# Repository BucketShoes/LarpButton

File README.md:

# LARP timer
Electronics project for live action roleplay, objective capture botton/timer.
Think like a chess clock, but more lights, bigger display, sound/voice callouts. Press and hold to capture an objective point, with time tracking.
ESP32 C6 based project, bluetooth admin interface for time tracking, number of swaps, team colors, and bluetooth beacons/player tracking.
PCB through JCLPCB, mostly from the basic parts list.
Built for battlecrylarp.org

# WORK IN PROGRESS
Note yet complete, untested.

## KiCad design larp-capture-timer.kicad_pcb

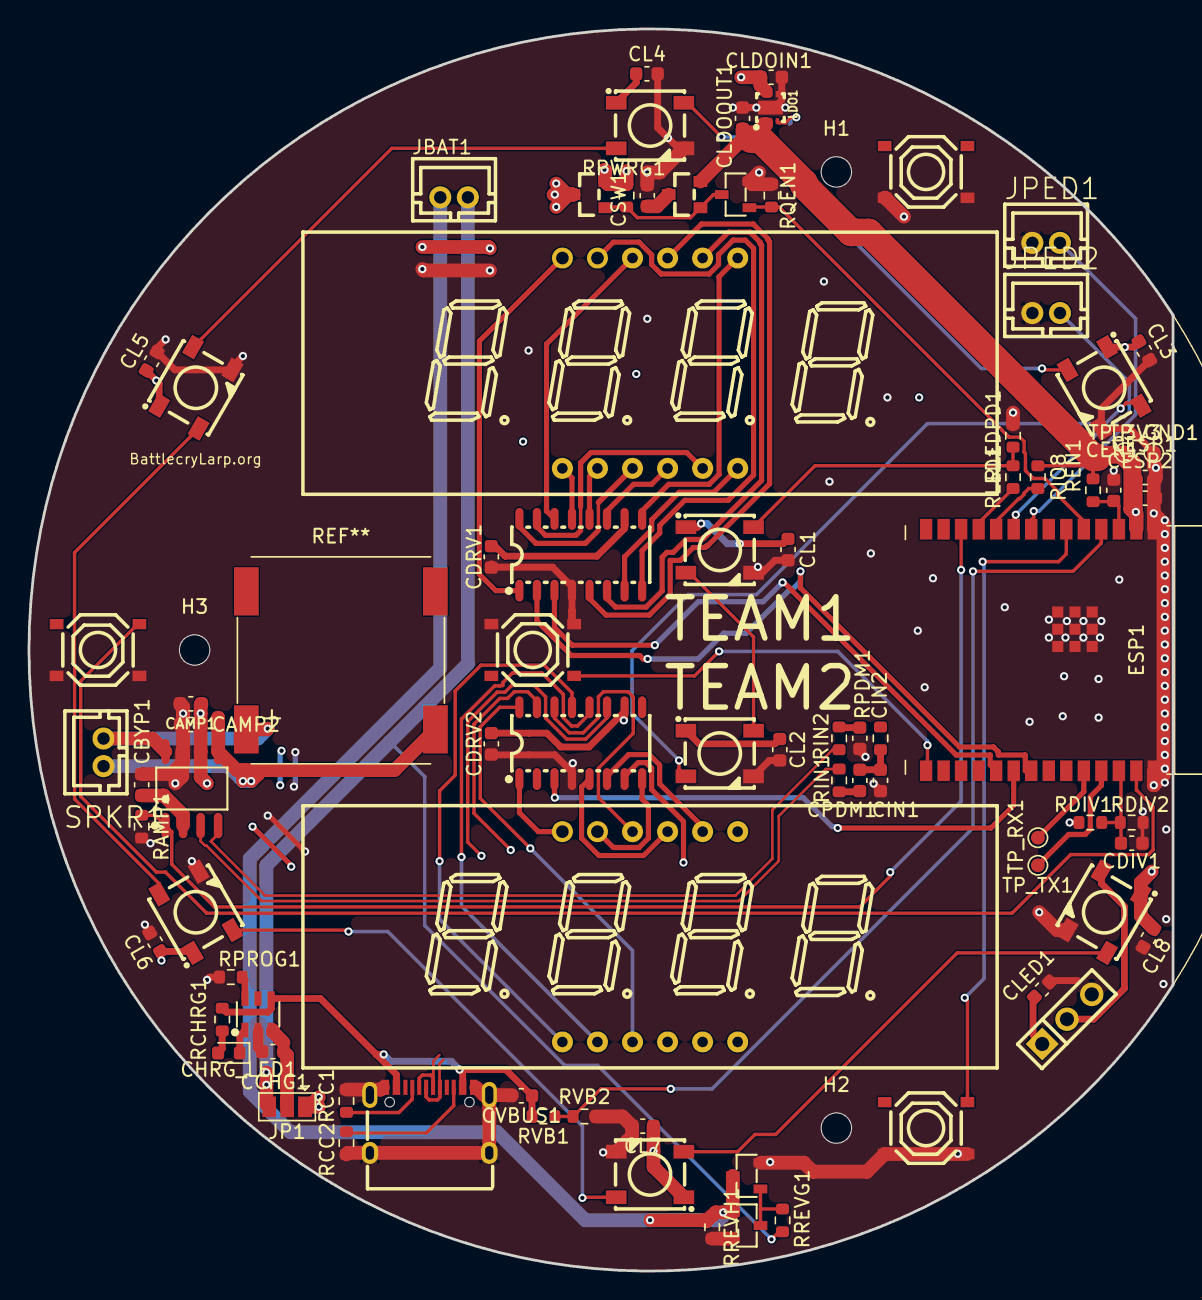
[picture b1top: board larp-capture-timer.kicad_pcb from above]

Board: 4 copper layers, 82.9 x 90.0 mm, 87 parts (1 on the bottom side), 78 nets.

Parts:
AMP1: NS4150C; SOP-8_L4.9-W3.9-P1.27-LS6.0-BL_NS4150C
BOOT1: TS-1187A-B-A-B; SW-SMD_4P-L5.1-W5.1-P3.70-LS6.5-TL_H1.5
BTN1, BTN2, BTN3: TS-1187A-B-A-B; SW-SMD_4P-L5.1-W5.1-P3.70-LS6.5-TL_H1.5
CAMP1: 10uF; C_0603_1608Metric
CAMP2: 1uF; C_0603_1608Metric
CBYP1: 1uF; C_0603_1608Metric
CCHG1: 10uF; C_0603_1608Metric
CDIV1: 100nF; C_0603_1608Metric
CDRV1, CDRV2: 100nF; C_0603_1608Metric
CELL1: BH-18650-B6AA002; BATTERY-SMD_18650-1S-L77.1-W20.7-1
CEN1: 1uF; C_0603_1608Metric
CESP1: 10uF; C_0603_1608Metric
CESP2: 100nF; C_0603_1608Metric
CHRG1: TP4057-42-SOT26-R; SOT-23-6_L2.9-W1.6-P0.95-LS2.8-BL_TP4057-42-SOT26-R
CHRG_LED1: Red; LED_0603_KA
CIN1, CIN2: 100nF; C_0603_1608Metric
CL1, CL2, CL3, CL4, CL5, CL6, CL7, CL8: 100nF; C_0603_1608Metric
CLDOIN1: 10uF; C_0603_1608Metric
CLDOOUT1: 10uF; C_0603_1608Metric
CLED1: 10uF; C_0603_1608Metric
CPDM1: 10nF; C_0603_1608Metric
CSW1: 10uF; C_0603_1608Metric
CVBUS1: 10uF; C_0603_1608Metric
DISP1, DISP2: FJ5462AH; LED-SEG-TH_12P-L50.3-W19.0-P2.54-S15.24-BL_FJ5462AH
DRV1, DRV2: GN1650; SOP-16_L9.9-W3.9-P1.27-LS6.1-BL_GN1650
ESP1: ESP32-C6-WROOM-1-N8; ESP32-C6-WROOM-1
H1, H2, H3: M2; MountingHole_2.2mm_M2
JBAT1: B2B-PH-K-S; CONN-TH_B2B-PH-K-S
JLEDX1: LED ext 1x3; HDR-TH_3P-P2.54-V-M_PZ254V-11-03P
JP1: SolderJumper_3; SolderJumper-3_P1.3mm_Open_Pad1.0x1.5mm
JPED1, JPED2: B2B-PH-K-S; CONN-TH_B2B-PH-K-S
LDO1: XC6220B331ER-G; USP-6C_L2.0-W1.8-P0.50-BL-EP_XC6220B331ER-G
LED1, LED2, LED3, LED4, LED5, LED6, LED7, LED8: WS2812B-B-V6; LED-SMD_4P-L5.0-W5.0-TL_WS2812B-B_WS2812B-B-V6
QBAT1: AO3401A; SOT-23_L2.9-W1.3-P1.90-LS2.4-BR_AO3401A
QEN1: AO3400A; SOT-23-3_L2.9-W1.3-P1.90-LS2.4-BR_AO3400A
QREV1: AO3400A; SOT-23-3_L2.9-W1.3-P1.90-LS2.4-BR_AO3400A
QREVH1: AO3400A; SOT-23-3_L2.9-W1.3-P1.90-LS2.4-BR_AO3400A
QSW1: AO3401A; SOT-23_L2.9-W1.3-P1.90-LS2.4-BR_AO3401A
RAMP1: 100k; R_0603_1608Metric
RCC1, RCC2: 5.1k; R_0603_1608Metric
RCHRG1: 1k; R_0603_1608Metric
RDIV1, RDIV2: 100k; R_0603_1608Metric
REN1: 10k; R_0603_1608Metric
RIN1, RIN2: 100k; R_0603_1608Metric
RIO8: 10k; R_0603_1608Metric
RLED1: 1k; R_0603_1608Metric
RLEDPD1: 100k; R_0603_1608Metric
RPDM1: 1k; R_0603_1608Metric
RPROG1: 2k; R_0603_1608Metric
RPWRG1: 100k; R_0603_1608Metric
RQEN1: 100k; R_0603_1608Metric
RREVG1: 100k; R_0603_1608Metric
RREVH1: 100k; R_0603_1608Metric
RVB1: 100k; R_0603_1608Metric
RVB2: 150k; R_0603_1608Metric
SPKR1: B2B-PH-K-S; CONN-TH_B2B-PH-K-S
TP_3V3: TestPoint; TestPoint_Pad_D1.0mm
TP_GND1: TestPoint; TestPoint_Pad_D1.0mm
TP_RX1: TestPoint; TestPoint_Pad_D1.0mm
TP_TX1: TestPoint; TestPoint_Pad_D1.0mm
USBC1: TYPE-C 16PIN 2MD(073); USB-C-SMD_TYPE-C-16PIN-2MD-073_TYPE-C16PIN2MD073

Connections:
/+3V3: CESP1.1, CESP2.1, CLDOOUT1.1, ESP1.2_3V3, LDO1.1_VOUT, LDO1.2_VOUT, QSW1.2_S, REN1.2, RIO8.2, TP_3V3.1
/+3V3_SW: CDRV1.1, CDRV2.1, CSW1.1, DRV1.10_VDD, DRV2.10_VDD, QSW1.3_D
/AMP_BYP: AMP1.2_BYPASS, CBYP1.1
/AMP_EN: AMP1.1_CTRL, ESP1.12_IO11, RAMP1.1
/AMP_INN: AMP1.4_INN, RIN2.1
/AMP_INP: AMP1.3_INP, RIN1.1
/CC1: RCC1.1, USBC1.4_CC1
/CC2: RCC2.1, USBC1.10_CC2
/CELL_N: CELL1.1_-, JBAT1.2, QREV1.3_D, QREVH1.1_G, RREVH1.1
/CHG_OUT: CCHG1.1, CHRG1.3_BAT, JP1.2
/CHRG_IND: CHRG1.1_CHRG, CHRG_LED1.1_K
/CHRG_LED_A: CHRG_LED1.2_A, RCHRG1.1
/DISP1_A: DISP1.11_A, DRV1.8_A
/DISP1_B: DISP1.7_B, DRV1.9_B
/DISP1_C: DISP1.4_C, DRV1.11_C
/DISP1_D: DISP1.2_D, DRV1.12_D
/DISP1_DIG1: DISP1.12_DIG1, DRV1.1_DIG1
/DISP1_DIG2: DISP1.9_DIG2, DRV1.5_DIG2
/DISP1_DIG3: DISP1.8_DIG3, DRV1.6_DIG3
/DISP1_DIG4: DISP1.6_DIG4, DRV1.7_DIG4
/DISP1_DP: DISP1.3_DP, DRV1.16_DP
/DISP1_E: DISP1.1_E, DRV1.13_E
/DISP1_F: DISP1.10_F, DRV1.14_F
/DISP1_G: DISP1.5_G, DRV1.15_G
/DISP2_A: DISP2.11_A, DRV2.8_A
/DISP2_B: DISP2.7_B, DRV2.9_B
/DISP2_C: DISP2.4_C, DRV2.11_C
/DISP2_D: DISP2.2_D, DRV2.12_D
/DISP2_DIG1: DISP2.12_DIG1, DRV2.1_DIG1
/DISP2_DIG2: DISP2.9_DIG2, DRV2.5_DIG2
/DISP2_DIG3: DISP2.8_DIG3, DRV2.6_DIG3
/DISP2_DIG4: DISP2.6_DIG4, DRV2.7_DIG4
/DISP2_DP: DISP2.3_DP, DRV2.16_DP
/DISP2_E: DISP2.1_E, DRV2.13_E
/DISP2_F: DISP2.10_F, DRV2.14_F
/DISP2_G: DISP2.5_G, DRV2.15_G
/DISP_CLK1: DRV1.2_CLK, ESP1.21_IO23
/DISP_CLK2: DRV2.2_CLK, ESP1.23_IO15
/DISP_DIO1: DRV1.3_DIO, ESP1.19_IO21
/DISP_DIO2: DRV2.3_DIO, ESP1.20_IO22
/EN: CEN1.1, ESP1.3_EN, REN1.1
/FACE_BTN1: BTN1.1, BTN1.2, ESP1.27_IO2
/FACE_BTN2: BTN2.1, BTN2.2, ESP1.6_IO6
/FACE_BTN3: BTN3.1, BTN3.2, ESP1.7_IO7
/INN_C: CIN2.1, RIN2.2
/INP_C: CIN1.1, RIN1.2
/IO8: ESP1.10_IO8, RIO8.1
/IO9_BOOT: BOOT1.1, BOOT1.2, ESP1.15_IO9
/LED_D2: LED1.2_DOUT, LED2.4_DIN
/LED_D3: LED2.2_DOUT, LED3.4_DIN
/LED_D4: LED3.2_DOUT, LED4.4_DIN
/LED_D5: LED4.2_DOUT, LED5.4_DIN
/LED_D6: LED5.2_DOUT, LED6.4_DIN
/LED_D7: LED6.2_DOUT, LED7.4_DIN
/LED_D8: LED7.2_DOUT, LED8.4_DIN
/LED_DIN: LED1.4_DIN, RLED1.2, RLEDPD1.1
/LED_DIN_MCU: ESP1.11_IO10, RLED1.1
/LED_XOUT: JLEDX1.2, LED8.2_DOUT
/PDM_FILT: CIN1.2, CPDM1.1, RPDM1.2
/PDM_OUT: ESP1.16_IO18, RPDM1.1
/PEDAL1: ESP1.8_IO0, JPED1.1
/PEDAL2: ESP1.9_IO1, JPED2.1
/PROG: CHRG1.6_PROG, RPROG1.1
/PWR_EN: ESP1.5_IO5, QEN1.1_G, RQEN1.1
/PWR_G: QBAT1.1_G, QEN1.3_D, QSW1.1_G, RPWRG1.1
/REV_G: QREV1.1_G, QREVH1.3_D, RREVG1.1
/RXD0: ESP1.24_RXD0, TP_RX1.1
/SPK_N: AMP1.5_VoN, SPKR1.2
/SPK_P: AMP1.8_VoP, SPKR1.1
/TXD0: ESP1.25_TXD0, TP_TX1.1
/USB_DN: ESP1.13_IO12, USBC1.5_DN2, USBC1.7_DN1
/USB_DP: ESP1.14_IO13, USBC1.6_DP1, USBC1.8_DP2
/VBAT: CELL1.2_+, CLDOIN1.1, JBAT1.1, JP1.3, LDO1.3_CE, LDO1.5_VIN, LDO1.6_VIN, QBAT1.2_S, RPWRG1.2, RREVG1.2
/VBAT_SENSE: CDIV1.1, ESP1.26_IO3, RDIV1.1, RDIV2.1
/VBUS: CHRG1.4_VCC, CVBUS1.1, RCHRG1.2, RVB1.2, USBC1.2_VBUS, USBC1.11_VBUS
/VBUS_SENSE: ESP1.4_IO4, RVB1.1, RVB2.1
/VSYS: AMP1.6_VCC, CAMP1.1, CAMP2.1, CL1.1, CL2.1, CL3.1, CL4.1, CL5.1, CL6.1, CL7.1, CL8.1, CLED1.1, JLEDX1.1, JP1.1, LED1.1_VDD, LED2.1_VDD, LED3.1_VDD, LED4.1_VDD, LED5.1_VDD, LED6.1_VDD, LED7.1_VDD, LED8.1_VDD, QBAT1.3_D, RDIV1.2
GND: AMP1.7_GND, BOOT1.3, BOOT1.4, BTN1.3, BTN1.4, BTN2.3, BTN2.4, BTN3.3, BTN3.4, CAMP1.2, CAMP2.2, CBYP1.2, CCHG1.2, CDIV1.2, CDRV1.2, CDRV2.2, CEN1.2, CESP1.2, CESP2.2, CHRG1.2_GND, CIN2.2, CL1.2, CL2.2, CL3.2, CL4.2, CL5.2, CL6.2, CL7.2, CL8.2, CLDOIN1.2, CLDOOUT1.2, CLED1.2, CPDM1.2, CSW1.2, CVBUS1.2, DRV1.4_GND, DRV2.4_GND, ESP1.1_GND, ESP1.28_GND, ESP1.29_EPAD, JLEDX1.3, JPED1.2, JPED2.2, LDO1.4_VSS, LDO1.7_EP, LED1.3_VSS, LED2.3_VSS, LED3.3_VSS, LED4.3_VSS, LED5.3_VSS, LED6.3_VSS, LED7.3_VSS, LED8.3_VSS, QEN1.2_S, QREV1.2_S, QREVH1.2_S, RAMP1.2, RCC1.2, RCC2.2, RDIV2.2, RLEDPD1.2, RPROG1.2, RQEN1.2, RREVH1.2, RVB2.2, TP_GND1.1, USBC1.1_GND, USBC1.12_GND, USBC1.13_SHELL, USBC1.14_SHELL
